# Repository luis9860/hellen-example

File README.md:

# FAQ.

Q: How do I get latest hellen-one?

A: ``.github/workflows/update-hellen-one-reference.yaml`` is set to pull latest hellen daily!

Q: I get error 'Cannot stat xx-yy__zz.kicad_pcb: No such file' but files are right there?

A: please do not use dashes and underscore symbols in file names.

Q: Automation says that aux_axis_origin is missing?

A: aux_axis_origin is required, please place it in the appropriate corner.

Q: I get "Cannot parse position" with negative value?

A: Please move origin point into left-bottom corner of the board since we cannot parse negative coordinates at the moment. See https://github.com/andreika-git/hellen-one/issues/349

Q: I am placing an order with JLCPCB and component orientation all looks wrong?!

A: See https://github.com/rusefi/uaefi/?tab=readme-ov-file#q-ive-place-an-order-with-jlcpcb-and-i-see-scary-looking-wrong-orientation

Q: What about firmware?

A: See https://github.com/rusefi/fw-custom-hellen144-f4 and https://github.com/rusefi/rusefi/wiki/Custom-Firmware

Q: Automation seems to work but files are not updated?

A: automation requires that you use default branch 'main'

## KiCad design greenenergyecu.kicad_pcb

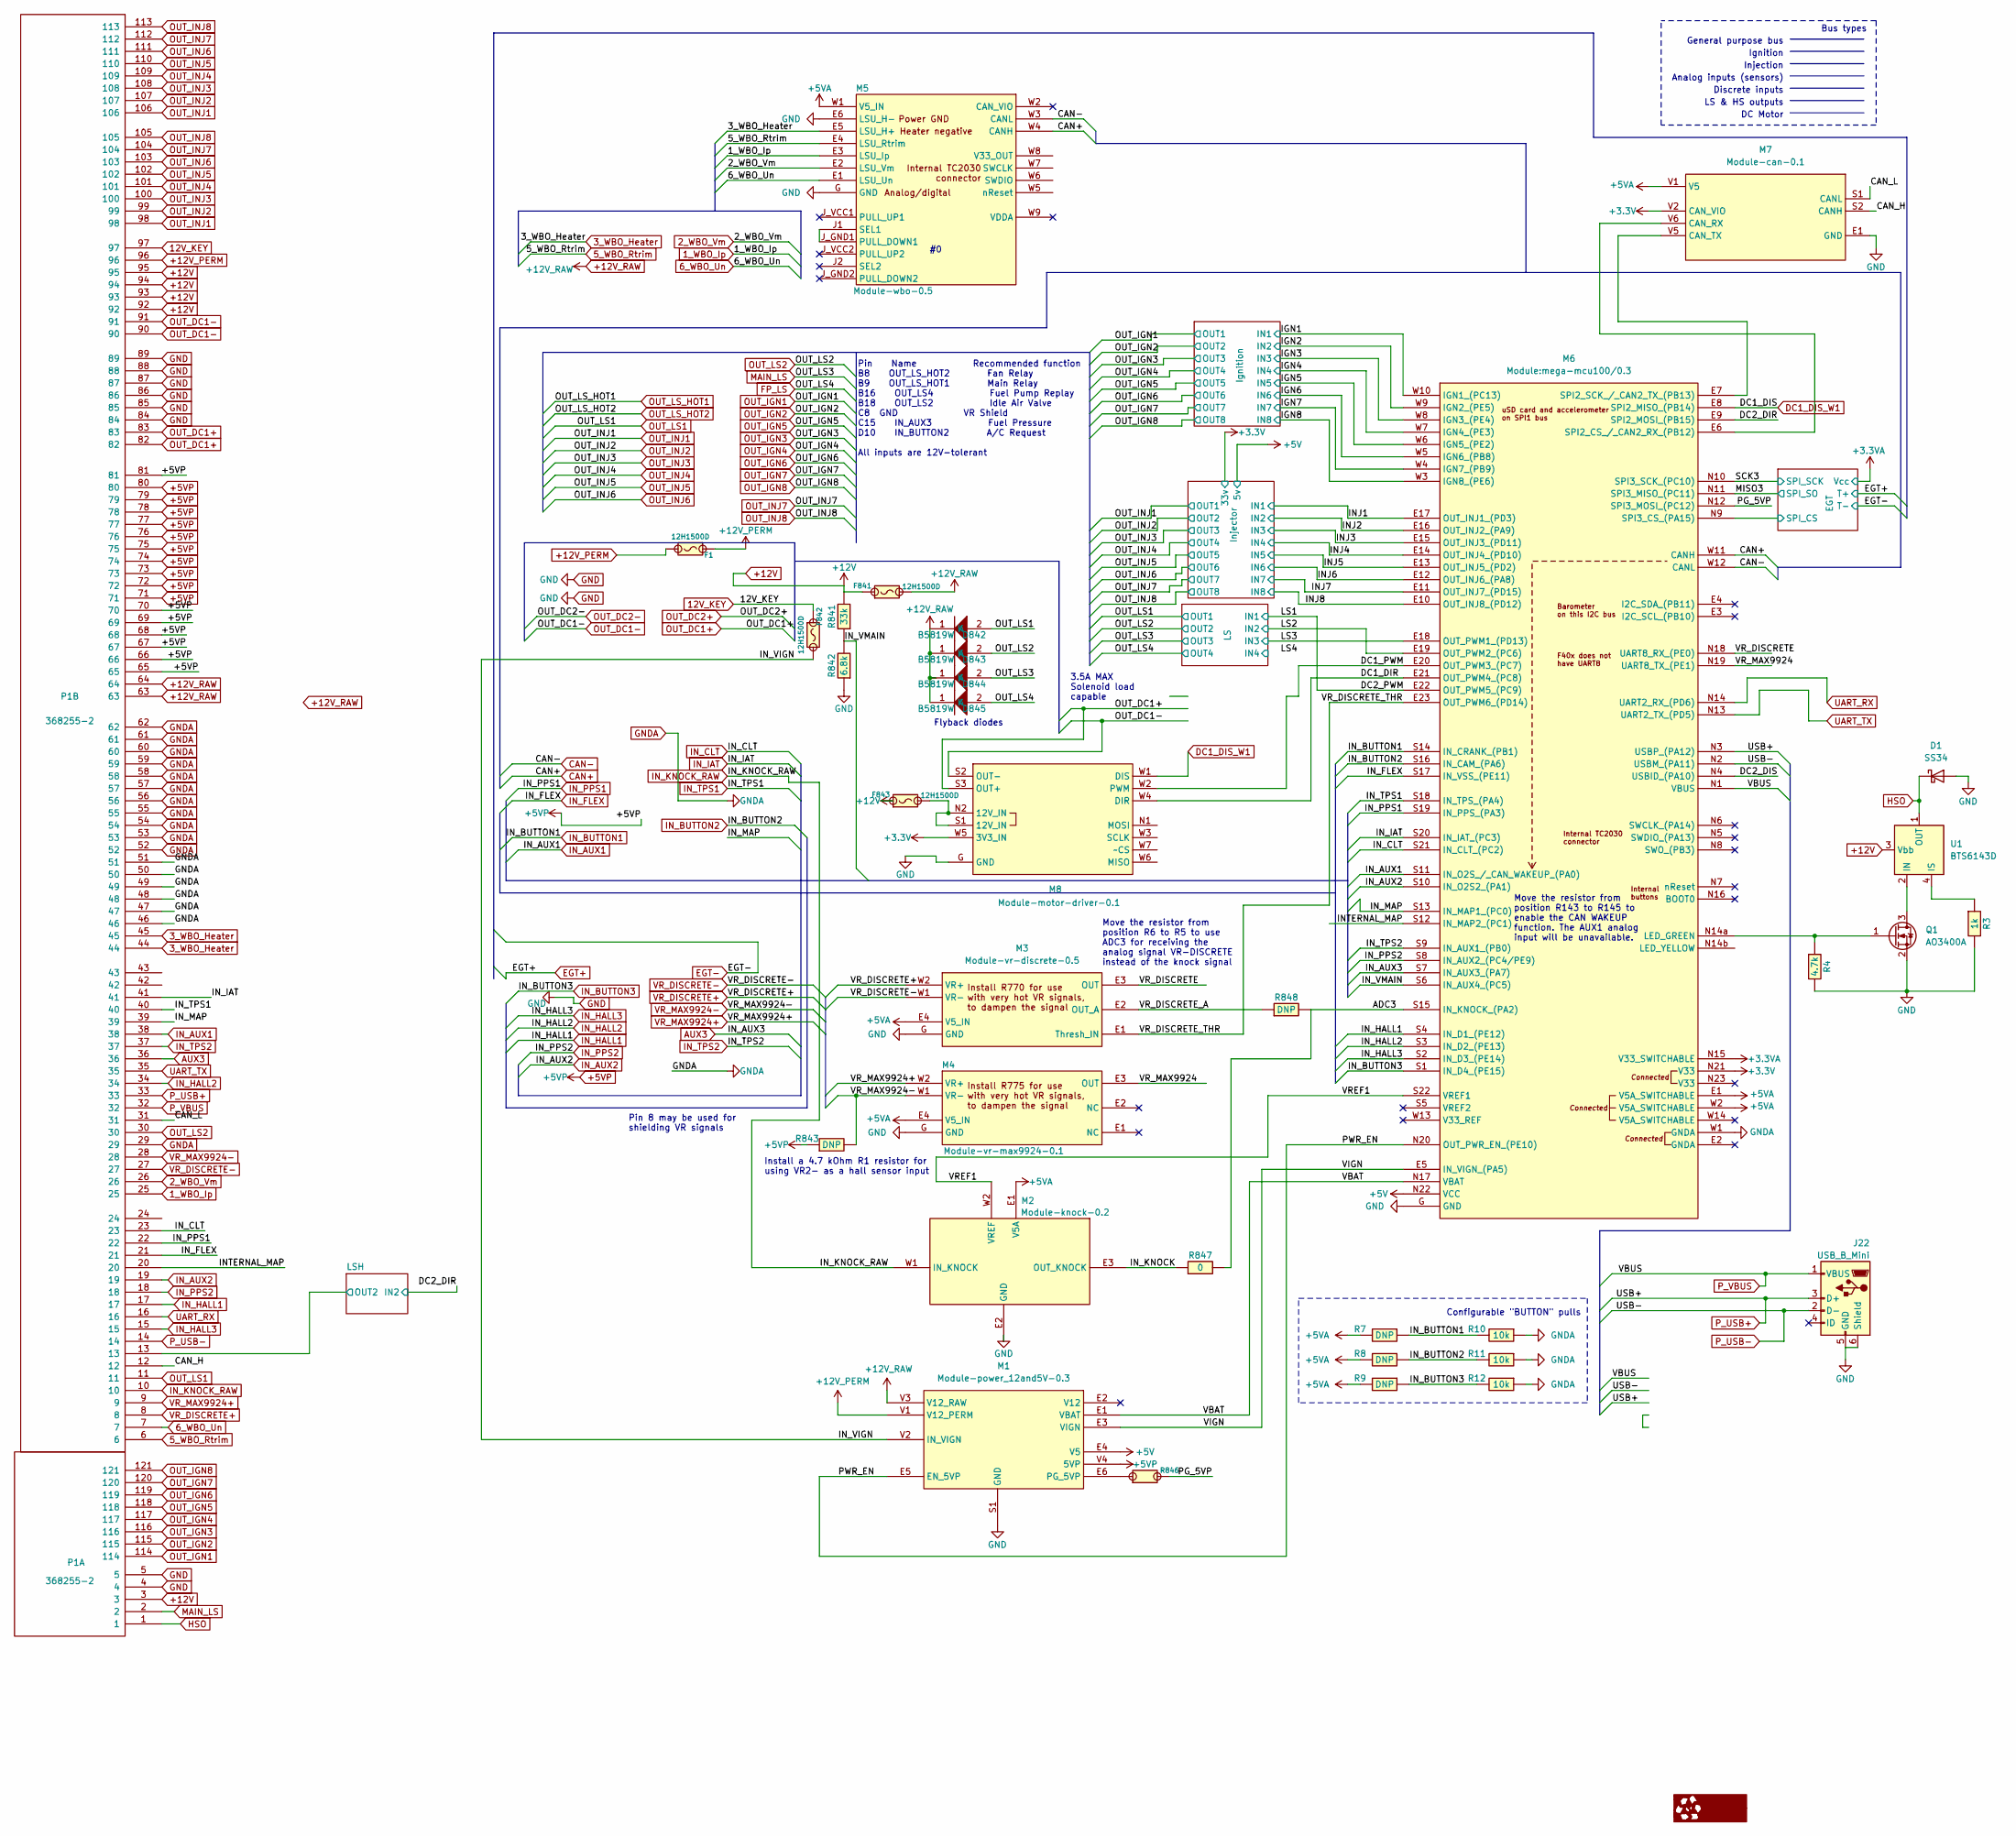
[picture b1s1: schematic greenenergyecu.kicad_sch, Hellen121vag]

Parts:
D1: SS34; D_SMA; LCSC C5119706
D842, D843, D844, D845: B5819W; SOD-123; LCSC C8598
F1, F841, F842, F843: 12H1500D; PAD-1206-PAD; LCSC C182446
J22: USB_B_Mini; USB-MINI-B-VERTICAL; LCSC C2682228
M1: Module-power_12and5V-0.3; power_12and5V
M2: Module-knock-0.2; knock
M3: Module-vr-discrete-0.5; vr-discrete
M4: Module-vr-max9924-0.1; vr-max9924
M5: Module-wbo-0.5; wbo
M6: Module:mega-mcu100/0.3; mega-mcu100
M7: Module-can-0.1; can
M8: Module-motor-driver-0.1; motor-driver
P1: 368255-2; LCSC C392284
Q1: AO3400A; SOT-23; LCSC C20917
R3: 1k; R0603; LCSC C21190
R4: 4.7k; R0603; LCSC C23162
R7, R8, R9: DNP; R0805
R10, R11, R12: 10k; R0805; LCSC C17414
R841: 33k; R0603; LCSC C4216
R842: 6.8k; R0603; LCSC C23212
R843: 4.7k; R0603
R846: Jumper-Pad-Pad; PAD-0805-PAD; LCSC C17477
R847: 0; R0603; LCSC C21189
R848: 0; R0603
U1: BTS6143D; TO-252-4; LCSC C95232

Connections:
1_WBO_Ip: M5.E3 (LSU_Ip), P1.25
2_WBO_Vm: M5.E2 (LSU_Vm), P1.26
3_WBO_Heater: M5.E5 (LSU_H+), P1.44, P1.45
5_WBO_Rtrim: M5.E4 (LSU_Rtrim), P1.6
6_WBO_Un: M5.E1 (LSU_Un), P1.7
12V_KEY: F842.1, P1.97
+3.3V: M6.N21 (V33), M7.V2 (CAN_VIO), M8.W5 (3V3_IN); also elsewhere on the board
+3.3VA: M6.N15 (V33_SWITCHABLE); also elsewhere on the board
+5V: M1.E4 (V5), M6.N22 (VCC); also elsewhere on the board
+5VA: M2.E1 (V5A), M3.E4 (V5_IN), M4.E4 (V5_IN), M5.W1 (V5_IN), M6.E1 (V5A_SWITCHABLE), M6.W2 (V5A_SWITCHABLE), M7.V1 (V5), R7.2, R8.2, R9.2
+5VP: M1.V4 (5VP), P1.65, P1.66, P1.67, P1.68, P1.69, P1.70, P1.71, P1.72, P1.73, P1.74, P1.75, P1.76, P1.77, P1.78, P1.79, P1.80, P1.81, R843.1
+12V: F841.1, F843.1, P1.3, P1.92, P1.93, P1.94, P1.95, R841.2, U1.3 (Vbb)
+12V_PERM: F1.1, F1.2, M1.V1 (V12_PERM), P1.96
+12V_RAW: D842.1 (K), D843.1 (K), D844.1 (K), D845.1 (K), F841.2, M1.V3 (V12_RAW), P1.63, P1.64
/ADC3: M6.S15 (IN_KNOCK_(PA2)), R847.2, R848.2
/CAN_H: M7.S2 (CANH), P1.12
/CAN_L: M7.S1 (CANL), P1.31
/DC1_DIR: M6.E21 (OUT_PWM4_(PC8)), M8.W4 (DIR)
/DC1_PWM: M6.E20 (OUT_PWM3_(PC7)), M8.W2 (PWM)
/DC2_DIR: M6.E9 (SPI2_MOSI_(PB15)); also elsewhere on the board
/DC2_DIS: M6.N4 (USBID_(PA10))
/DC2_PWM: M6.E22 (OUT_PWM5_(PC9)); also elsewhere on the board
/EGT/SPI_CS: M6.N9 (SPI3_CS_(PA15)); also elsewhere on the board
/IGN1: M6.W10 (IGN1_(PC13)); also elsewhere on the board
/IGN2: M6.W9 (IGN2_(PE5)); also elsewhere on the board
/IGN3: M6.W8 (IGN3_(PE4)); also elsewhere on the board
/IGN4: M6.W7 (IGN4_(PE3)); also elsewhere on the board
/IGN5: M6.W6 (IGN5_(PE2)); also elsewhere on the board
/IGN6: M6.W5 (IGN6_(PB8)); also elsewhere on the board
/IGN7: M6.W4 (IGN7_(PB9)); also elsewhere on the board
/IGN8: M6.W3 (IGN8_(PE6)); also elsewhere on the board
/INJ1: M6.E17 (OUT_INJ1_(PD3)); also elsewhere on the board
/INJ2: M6.E16 (OUT_INJ2_(PA9)); also elsewhere on the board
/INJ3: M6.E15 (OUT_INJ3_(PD11)); also elsewhere on the board
/INJ4: M6.E14 (OUT_INJ4_(PD10)); also elsewhere on the board
/INJ5: M6.E13 (OUT_INJ5_(PD2)); also elsewhere on the board
/INJ6: M6.E12 (OUT_INJ6_(PA8)); also elsewhere on the board
/INJ7: M6.E11 (OUT_INJ7_(PD15)); also elsewhere on the board
/INJ8: M6.E10 (OUT_INJ8_(PD12)); also elsewhere on the board
/INTERNAL_MAP: M6.S12 (IN_MAP2_(PC1)), P1.20
/IN_KNOCK: M2.E3 (OUT_KNOCK), R847.1
/IN_MAP: M6.S13 (IN_MAP1_(PC0)), P1.39
/IN_VIGN: F842.2, M1.V2 (IN_VIGN)
/IN_VMAIN: M6.S6 (IN_AUX4_(PC5)), R841.1, R842.2
/LS2: M6.E19 (OUT_PWM2_(PC6)); also elsewhere on the board
/LS3: M6.E18 (OUT_PWM1_(PD13)); also elsewhere on the board
/LSH/OUT2: P1.13; also elsewhere on the board
/MISO3: M6.N11 (SPI3_MISO_(PC11)); also elsewhere on the board
/PG_5VP: M6.N12 (SPI3_MOSI_(PC12)), R846.2
/PWR_EN: M1.E5 (EN_5VP), M6.N20 (OUT_PWR_EN_(PE10))
/SCK3: M6.N10 (SPI3_SCK_(PC10)); also elsewhere on the board
/VBAT: M1.E1 (VBAT), M6.N17 (VBAT)
/VIGN: M1.E3 (VIGN), M6.E5 (IN_VIGN_(PA5))
/VREF1: M2.W2 (VREF), M6.S22 (VREF1)
/VR_DISCRETE: M3.E3 (OUT), M6.N18 (UART8_RX_(PE0))
/VR_DISCRETE_A: M3.E2 (OUT_A), R848.1
/VR_DISCRETE_THR: M3.E1 (Thresh_IN), M6.E23 (OUT_PWM6_(PD14))
/VR_MAX9924: M4.E3 (OUT), M6.N19 (UART8_TX_(PE1))
AUX3: M6.S7 (IN_AUX3_(PA7)), P1.36
CAN+: M5.W4 (CANH), M6.W11 (CANH)
CAN-: M5.W3 (CANL), M6.W12 (CANL)
DC1_DIS_W1: M6.E8 (SPI2_MISO_(PB14)), M8.W1 (DIS)
FP_LS: D845.2 (A); also elsewhere on the board
GND: D1.2 (A), J22.5 (GND), J22.6 (Shield), M1.S1 (GND), M2.E2 (GND), M3.G (GND), M4.G (GND), M5.E6 (LSU_H-), M5.G (GND), M6.G (GND), M7.E1 (GND), M8.G (GND), P1.4, P1.5, P1.84, P1.85, P1.86, P1.87, P1.88, P1.89, Q1.2 (S), R3.2, R4.2, R842.1; also elsewhere on the board
GNDA: M6.W1 (GNDA), P1.29, P1.46, P1.47, P1.48, P1.49, P1.50, P1.51, P1.52, P1.53, P1.54, P1.55, P1.56, P1.57, P1.58, P1.59, P1.60, P1.61, P1.62, R10.1, R11.1, R12.1
HSO: D1.1 (K), P1.1, U1.1 (OUT), U1.5 (OUT)
IN_AUX1: M6.S11 (IN_O2S_/_CAN_WAKEUP_(PA0)), P1.38
IN_AUX2: M6.S10 (IN_O2S2_(PA1)), P1.19
IN_BUTTON1: M6.S14 (IN_CRANK_(PB1)), R7.1, R10.2
IN_BUTTON2: M6.S16 (IN_CAM_(PA6)), R8.1, R11.2
IN_BUTTON3: M6.S1 (IN_D4_(PE15)), R9.1, R12.2
IN_CLT: M6.S21 (IN_CLT_(PC2)), P1.23
IN_FLEX: M6.S17 (IN_VSS_(PE11)), P1.21
IN_HALL1: M6.S4 (IN_D1_(PE12)), P1.17
IN_HALL2: M6.S3 (IN_D2_(PE13)), P1.34
IN_HALL3: M6.S2 (IN_D3_(PE14)), P1.15
IN_IAT: M6.S20 (IN_IAT_(PC3)), P1.41
IN_KNOCK_RAW: M2.W1 (IN_KNOCK), P1.10
IN_PPS1: M6.S19 (IN_PPS_(PA3)), P1.22
IN_PPS2: M6.S8 (IN_AUX2_(PC4/PE9)), P1.18
IN_TPS1: M6.S18 (IN_TPS_(PA4)), P1.40
IN_TPS2: M6.S9 (IN_AUX1_(PB0)), P1.37
MAIN_LS: D844.2 (A), P1.2; also elsewhere on the board
unnamed: F843.2, M8.N2 (12V_IN), M8.S1 (12V_IN)
unnamed: M1.E6 (PG_5VP), R846.1
unnamed: M5.J1 (SEL1), M5.J_GND1 (PULL_DOWN1)
unnamed: M6.N14a (LED_GREEN), Q1.1 (G), R4.1
unnamed: M6.E6 (SPI2_CS_/_CAN2_RX_(PB12)), M7.V6 (CAN_RX)
unnamed: M6.E7 (SPI2_SCK_/_CAN2_TX_(PB13)), M7.V5 (CAN_TX)
unnamed: Q1.3 (D), U1.2 (IN)
unnamed: R3.1, U1.4 (IS)
OUT_DC1+: M8.S3 (OUT+), P1.82, P1.83
OUT_DC1-: M8.S2 (OUT-), P1.90, P1.91
OUT_IGN1: P1.114; also elsewhere on the board
OUT_IGN2: P1.115; also elsewhere on the board
OUT_IGN3: P1.116; also elsewhere on the board
OUT_IGN4: P1.117; also elsewhere on the board
OUT_IGN5: P1.118; also elsewhere on the board
OUT_IGN6: P1.119; also elsewhere on the board
OUT_IGN7: P1.120; also elsewhere on the board
OUT_IGN8: P1.121; also elsewhere on the board
OUT_INJ1: P1.98, P1.106; also elsewhere on the board
OUT_INJ2: P1.99, P1.107; also elsewhere on the board
OUT_INJ3: P1.100, P1.108; also elsewhere on the board
OUT_INJ4: P1.101, P1.109; also elsewhere on the board
OUT_INJ5: P1.102, P1.110; also elsewhere on the board
OUT_INJ6: P1.103, P1.111; also elsewhere on the board
OUT_INJ7: P1.104, P1.112; also elsewhere on the board
OUT_INJ8: P1.105, P1.113; also elsewhere on the board
OUT_LS1: D842.2 (A), P1.11; also elsewhere on the board
OUT_LS2: D843.2 (A), P1.30; also elsewhere on the board
P_USB+: J22.3 (D+), M6.N3 (USBP_(PA12)), P1.33
P_USB-: J22.2 (D-), M6.N2 (USBM_(PA11)), P1.14
P_VBUS: J22.1 (VBUS), M6.N1 (VBUS), P1.32
UART_RX: M6.N14 (UART2_RX_(PD6)), P1.16
UART_TX: M6.N13 (UART2_TX_(PD5)), P1.35
VR_DISCRETE+: M3.W2 (VR+), P1.8
VR_DISCRETE-: M3.W1 (VR-), P1.27
VR_MAX9924+: M4.W2 (VR+), P1.9
VR_MAX9924-: M4.W1 (VR-), P1.28, R843.2

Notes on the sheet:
Analog inputs (sensors)
Install a 4.7 kOhm R1 resistor for using VR2- as a hall sensor input
Injection
Pin Name Recommended function B8 OUT_LS_HOT2 Fan Relay B9 OUT_LS_HOT1 Main Relay B16 OUT_LS4 Fuel Pump Replay B18 OUT_LS2 Idle Air Valve C8 GND VR Shield C15 IN_AUX3 Fuel Pressure D10 IN_BUTTON2 A/C Request All inputs are 12V-tolerant
Ignition
Move the resistor from position R143 to R145 to enable the CAN WAKEUP function. The AUX1 analog input will be unavailable.
Flyback diodes
DC Motor
Discrete inputs
3.5A MAX Solenoid load capable
Pin 8 may be used for shielding VR signals
General purpose bus
Bus types
Configurable "BUTTON" pulls
LS & HS outputs
Move the resistor from position R6 to R5 to use ADC3 for receiving the analog signal VR-DISCRETE instead of the knock signal

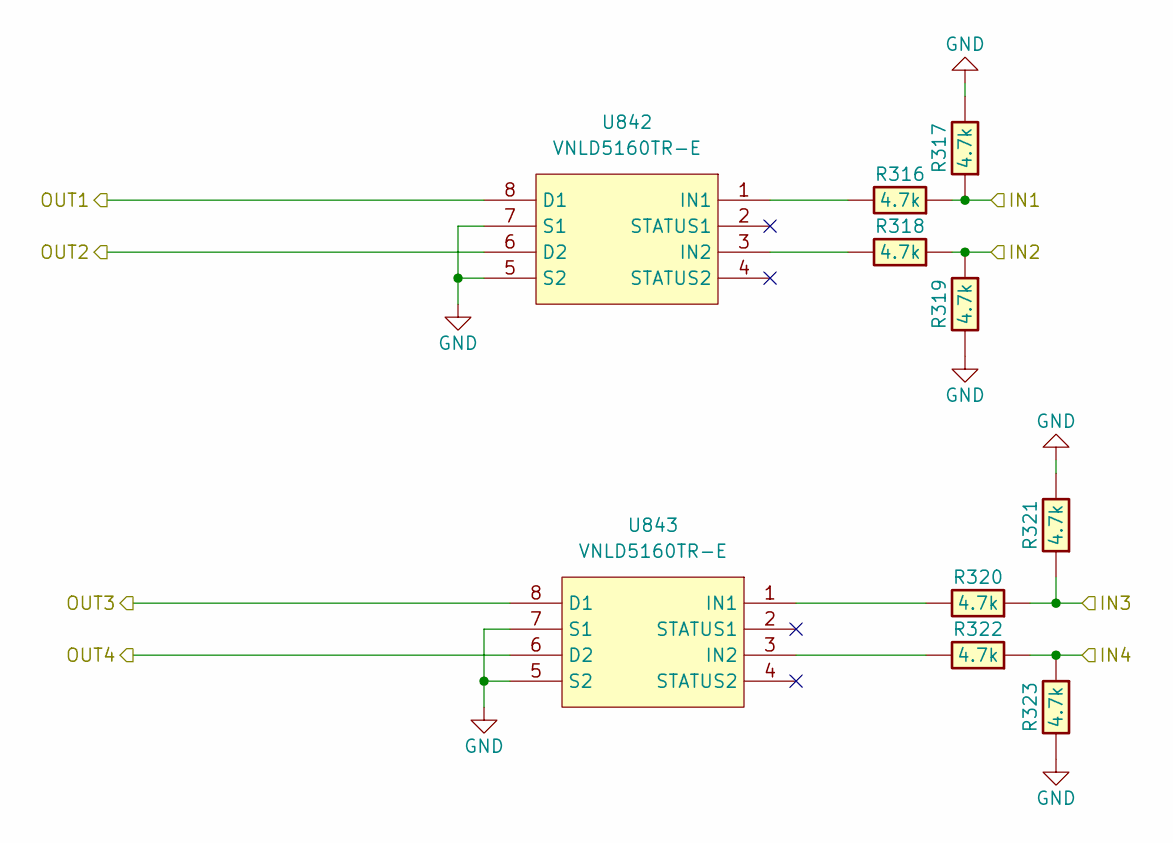
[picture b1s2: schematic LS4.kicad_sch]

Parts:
R316, R317, R318, R319, R320, R321, R322, R323: 4.7k; R0603; LCSC C23162
U842, U843: VNLD5160TR-E; SOIC-8_3.9x4.9mm_P1.27mm; LCSC C377942

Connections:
/DC2_PWM: R316.1, R317.1; also elsewhere on the board
/LS2: R318.1, R319.1; also elsewhere on the board
/LS3: R320.1, R321.1; also elsewhere on the board
/LS/IN4: R322.1, R323.1
FP_LS: U843.6 (D2); also elsewhere on the board
GND: R317.2, R319.2, R321.2, R323.2, U842.5 (S2), U842.7 (S1), U843.5 (S2), U843.7 (S1); also elsewhere on the board
MAIN_LS: U843.8 (D1); also elsewhere on the board
unnamed: R316.2, U842.1 (IN1)
unnamed: R318.2, U842.3 (IN2)
unnamed: R320.2, U843.1 (IN1)
unnamed: R322.2, U843.3 (IN2)
OUT_LS1: U842.8 (D1); also elsewhere on the board
OUT_LS2: U842.6 (D2); also elsewhere on the board

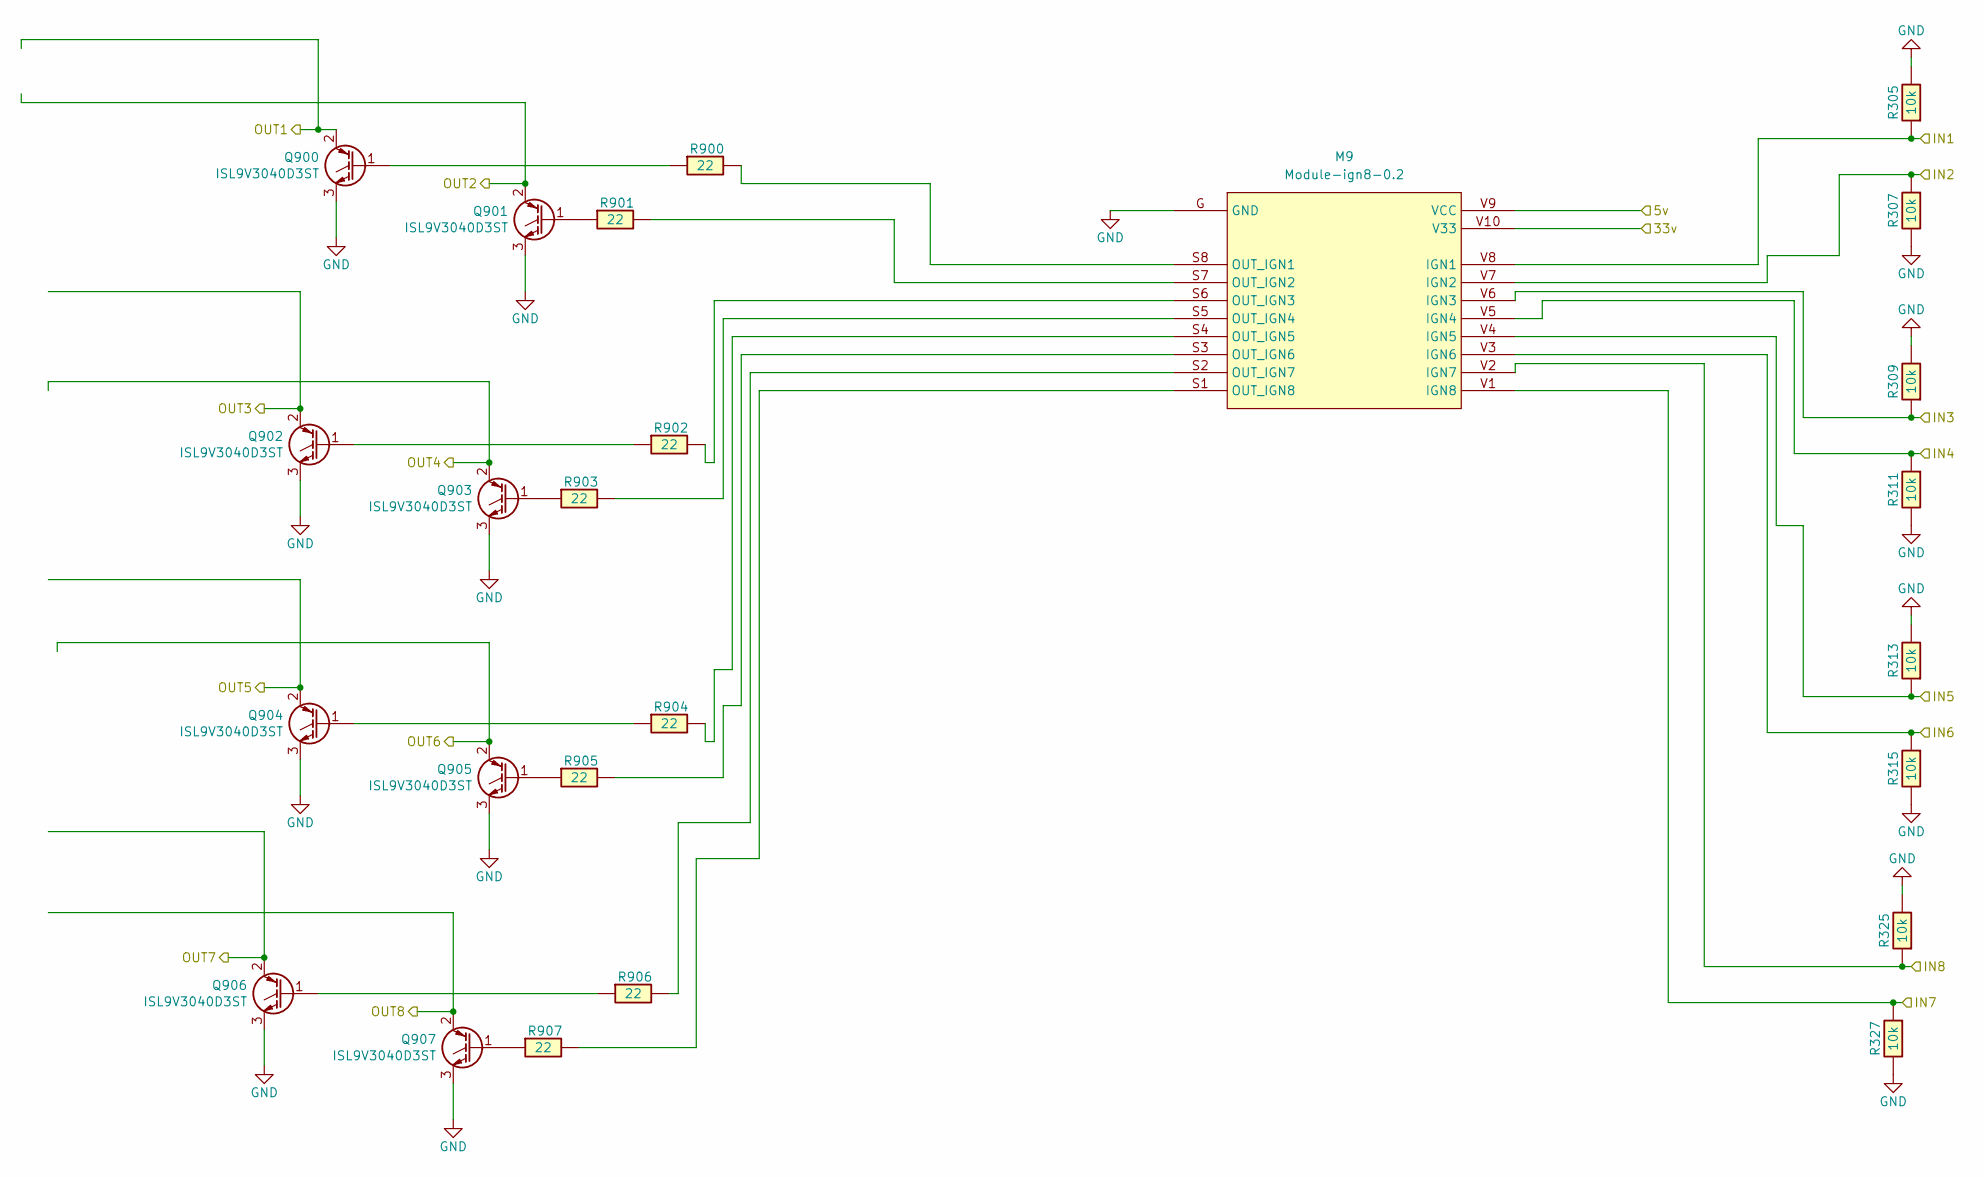
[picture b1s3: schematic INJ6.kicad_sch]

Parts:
M9: Module-ign8-0.2; ign8
Q900, Q902, Q903, Q904, Q905, Q906, Q907: ISL9V3040D3ST; TO-252-2; LCSC C5350881
Q901: ISL9V3040D3ST; abel-252-2; LCSC C5350881
R305, R307, R309, R311, R313, R315, R325, R327: 10k; R0603; LCSC C17414
R900, R901, R902, R903, R904, R905, R906, R907: 22; R0603; LCSC C23345

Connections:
+3.3V: M9.V10 (V33); also elsewhere on the board
+5V: M9.V9 (VCC); also elsewhere on the board
/INJ1: M9.V8 (IGN1), R305.1; also elsewhere on the board
/INJ2: M9.V7 (IGN2), R307.1; also elsewhere on the board
/INJ3: M9.V6 (IGN3), R309.1; also elsewhere on the board
/INJ4: M9.V5 (IGN4), R311.1; also elsewhere on the board
/INJ5: M9.V4 (IGN5), R313.1; also elsewhere on the board
/INJ6: M9.V3 (IGN6), R315.1; also elsewhere on the board
/INJ7: M9.V1 (IGN8), R327.1; also elsewhere on the board
/INJ8: M9.V2 (IGN7), R325.1; also elsewhere on the board
GND: M9.G (GND), Q900.3 (E), Q901.3 (E), Q902.3 (E), Q903.3 (E), Q904.3 (E), Q905.3 (E), Q906.3 (E), Q907.3 (E), R305.2, R307.2, R309.2, R311.2, R313.2, R315.2, R325.2, R327.2; also elsewhere on the board
unnamed: M9.S8 (OUT_IGN1), R900.2
unnamed: M9.S7 (OUT_IGN2), R901.2
unnamed: M9.S6 (OUT_IGN3), R902.2
unnamed: M9.S5 (OUT_IGN4), R903.2
unnamed: M9.S4 (OUT_IGN5), R904.2
unnamed: M9.S3 (OUT_IGN6), R905.2
unnamed: M9.S2 (OUT_IGN7), R906.2
unnamed: M9.S1 (OUT_IGN8), R907.2
unnamed: Q900.1 (G), R900.1
unnamed: Q901.1 (G), R901.1
unnamed: Q902.1 (G), R902.1
unnamed: Q903.1 (G), R903.1
unnamed: Q904.1 (G), R904.1
unnamed: Q905.1 (G), R905.1
unnamed: Q906.1 (G), R906.1
unnamed: Q907.1 (G), R907.1
OUT_INJ1: Q900.2 (C); also elsewhere on the board
OUT_INJ2: Q901.2 (C); also elsewhere on the board
OUT_INJ3: Q902.2 (C); also elsewhere on the board
OUT_INJ4: Q903.2 (C); also elsewhere on the board
OUT_INJ5: Q904.2 (C); also elsewhere on the board
OUT_INJ6: Q905.2 (C); also elsewhere on the board
OUT_INJ7: Q906.2 (C); also elsewhere on the board
OUT_INJ8: Q907.2 (C); also elsewhere on the board

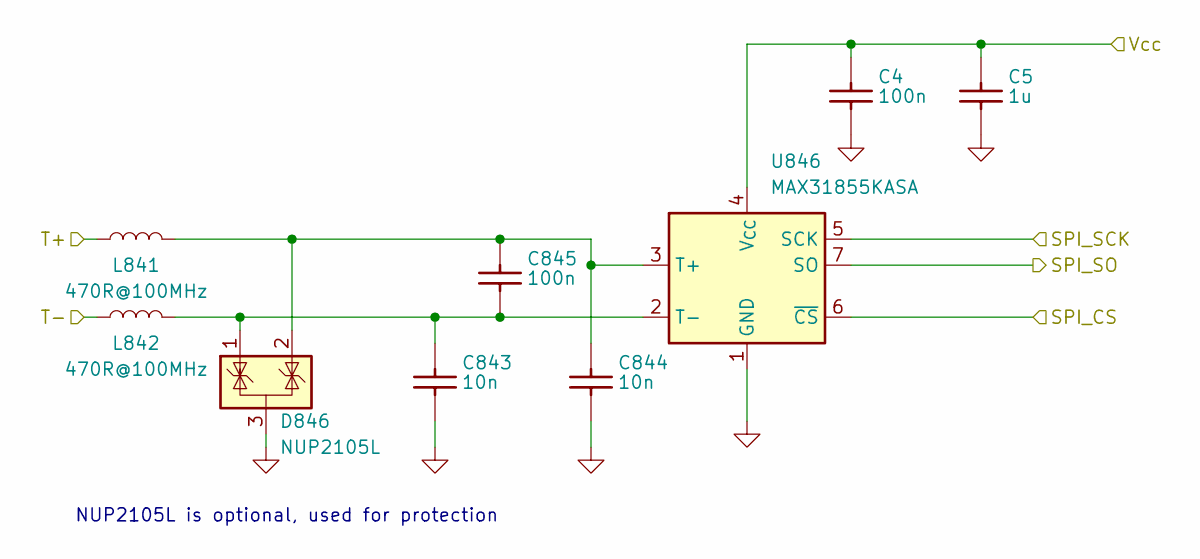
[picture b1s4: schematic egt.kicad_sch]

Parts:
C4, C845: 100n; C0603; LCSC C14663
C5: 1u; C0603; LCSC C15849
C843, C844: 10n; C0603; LCSC C57112
D846: NUP2105L; SOT-23; LCSC C284104
L841, L842: 470R@100MHz; L_0603_1608Metric; LCSC C97853
U846: MAX31855KASA; SOIC-8_3.9x4.9mm_P1.27mm; LCSC C52028

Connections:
+3.3VA: C4.2, C5.2, U846.4 (V_{CC}); also elsewhere on the board
/EGT/SPI_CS: U846.6 (~CS); also elsewhere on the board
/MISO3: U846.7 (SO); also elsewhere on the board
/SCK3: U846.5 (SCK); also elsewhere on the board
EGT+: L841.1
EGT-: L842.1
GND: C4.1, C5.1, C843.1, C844.1, D846.3 (A), U846.1 (GND); also elsewhere on the board
unnamed: C844.2, C845.2, D846.2 (K), L841.2, U846.3 (T+)
unnamed: C843.2, C845.1, D846.1 (K), L842.2, U846.2 (T-)

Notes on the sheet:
NUP2105L is optional, used for protection

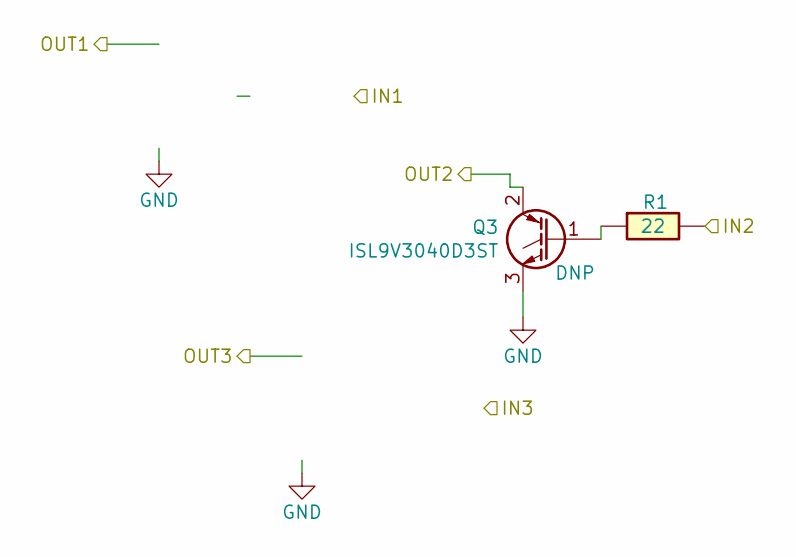
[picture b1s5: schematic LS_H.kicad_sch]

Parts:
Q3: ISL9V3040D3ST; TO-252-2
R1: 22; R0603; LCSC C23345

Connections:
/DC2_DIR: R1.2; also elsewhere on the board
/LSH/OUT2: Q3.2 (C); also elsewhere on the board
GND: Q3.3 (E); also elsewhere on the board
unnamed: Q3.1 (G), R1.1

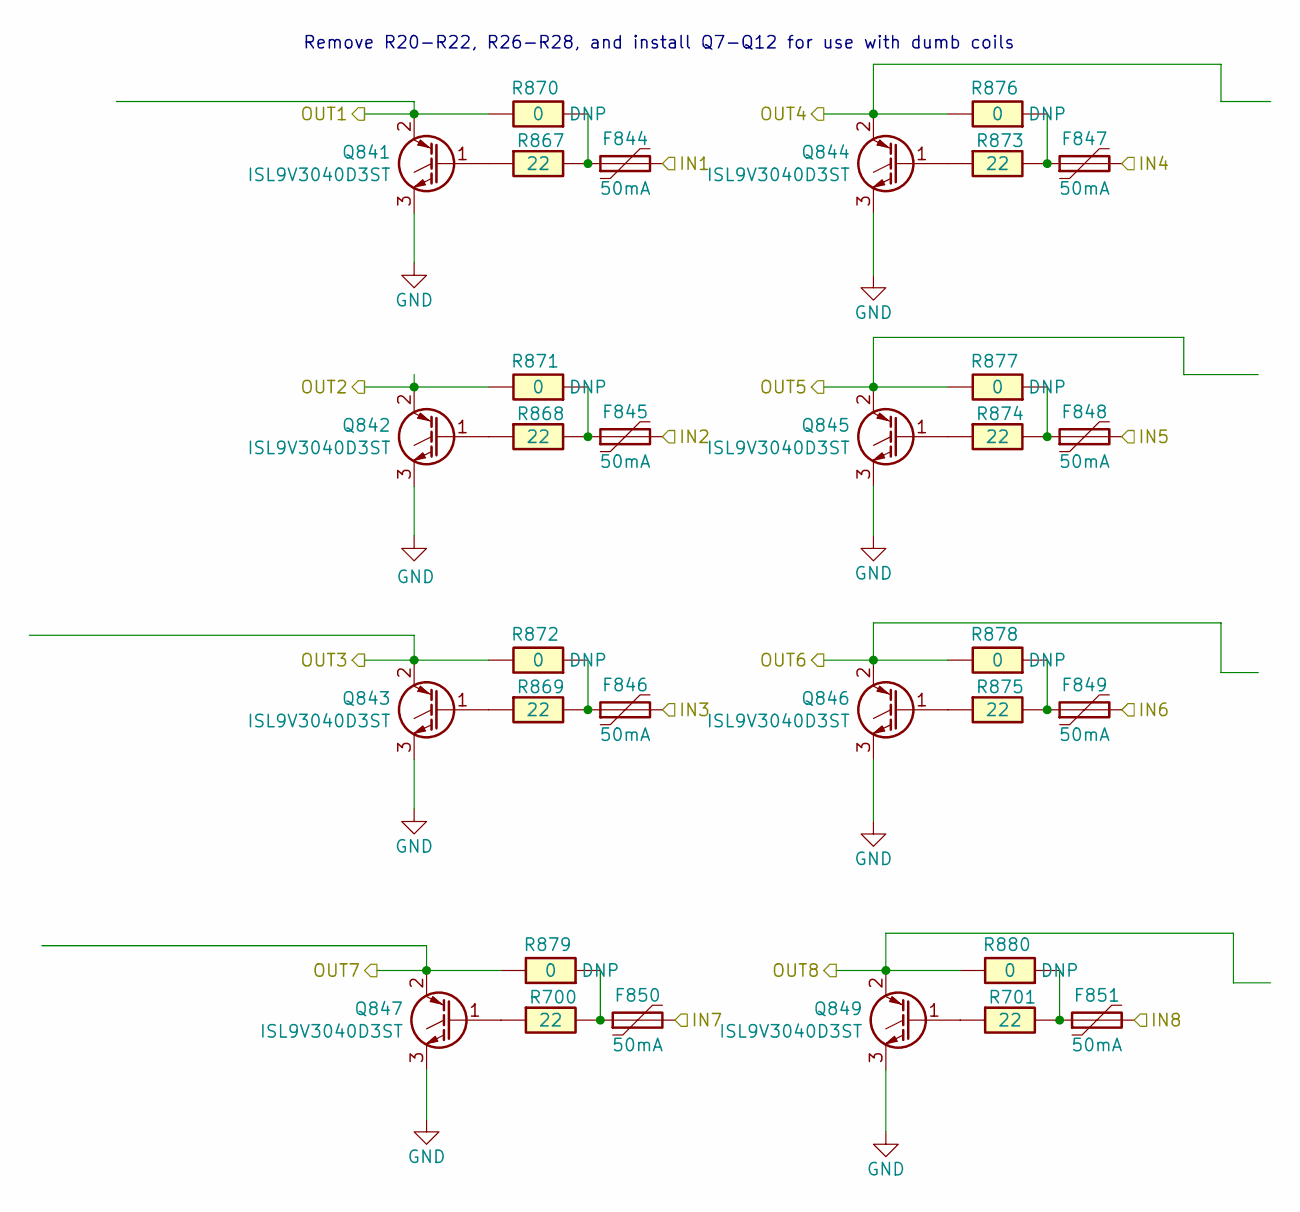
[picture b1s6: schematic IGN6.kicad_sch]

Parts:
F844, F845, F846, F847, F848, F849, F850, F851: 50mA; Fuse_0603_1608Metric; LCSC C369141
Q841, Q844, Q846, Q847: ISL9V3040D3ST; TO-252-2; LCSC C462128
Q842, Q843, Q845, Q849: ISL9V3040D3ST; MODIGBT; LCSC C462128
R700, R701, R867, R868, R869, R873, R874, R875: 22; R0603; LCSC C23345
R870, R871, R872, R876, R877, R878, R879, R880: 0; R_2512_6332Metric

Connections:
/IGN1: F844.2; also elsewhere on the board
/IGN2: F845.2; also elsewhere on the board
/IGN3: F846.2; also elsewhere on the board
/IGN4: F847.2; also elsewhere on the board
/IGN5: F848.2; also elsewhere on the board
/IGN6: F849.2; also elsewhere on the board
/IGN7: F850.2; also elsewhere on the board
/IGN8: F851.2; also elsewhere on the board
GND: Q841.3 (E), Q842.3 (E), Q843.3 (E), Q844.3 (E), Q845.3 (E), Q846.3 (E), Q847.3 (E), Q849.3 (E); also elsewhere on the board
unnamed: F844.1, R867.2, R870.1
unnamed: F845.1, R868.2, R871.1
unnamed: F846.1, R869.2, R872.1
unnamed: F847.1, R873.2, R876.1
unnamed: F848.1, R874.2, R877.1
unnamed: F849.1, R875.2, R878.1
unnamed: F850.1, R700.2, R879.1
unnamed: F851.1, R701.2, R880.1
unnamed: Q841.1 (G), R867.1
unnamed: Q842.1 (G), R868.1
unnamed: Q843.1 (G), R869.1
unnamed: Q844.1 (G), R873.1
unnamed: Q845.1 (G), R874.1
unnamed: Q846.1 (G), R875.1
unnamed: Q847.1 (G), R700.1
unnamed: Q849.1 (G), R701.1
OUT_IGN1: Q841.2 (C), R870.2; also elsewhere on the board
OUT_IGN2: Q842.2 (C), R871.2; also elsewhere on the board
OUT_IGN3: Q843.2 (C), R872.2; also elsewhere on the board
OUT_IGN4: Q844.2 (C), R876.2; also elsewhere on the board
OUT_IGN5: Q845.2 (C), R877.2; also elsewhere on the board
OUT_IGN6: Q846.2 (C), R878.2; also elsewhere on the board
OUT_IGN7: Q847.2 (C), R879.2; also elsewhere on the board
OUT_IGN8: Q849.2 (C), R880.2; also elsewhere on the board

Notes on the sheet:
Remove R20-R22, R26-R28, and install Q7-Q12 for use with dumb coils

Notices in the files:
greenenergy_ecu.kicad_pcb:
© andreika, 2021
